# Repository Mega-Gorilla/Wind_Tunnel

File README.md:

# Wind Tunnel

**株式会社ながれ技術研究所の「オープンソース風洞 / MyWindTunnel」の吸込型風洞をベースに開発しています。** 原設計と風洞本体のCADは、[公式のMyWindTunnelページ](https://nagare-giken.jp/mywindtunnel/)から取得してください。原設計の公開に感謝します。

このリポジトリは、独自の電子回路・制御ソフト・追加固定部品と、その検証資料をまとめたものです。**公式配布の風洞CADは同梱しません。** 本体を含む結合CADや、その形状を変換・抽出したデータも配布対象にしません。独自部品のCAD、回路図、測定結果・図・報告書は別の公開対象として扱います。

現行基板は **Pico Carrier Rev E**、制御ソフトは **0.3.0 実機有限運転版・タッチ操作対応**です。

## 原設計からの変更

- ファンをARCTIC P12 MaxからP14 Pro PSTへ変更。
- Raspberry Pi Picoによるセンサー接続・回転数取得・ファン制御と、独自のPico Carrier基板を追加。
- Raspberry Pi上のタッチUIと、遠隔モードON/OFF・許可IP・APIトークン認証を備えたAPIを追加。
- 画面・基板・電源を固定する独自の樹脂部品を設計。

これらの変更を含む装置の測定結果は、原設計の性能値と同一ではありません。公式サイトの名称に「オープンソース」を含むことから、CADの再配布許諾を独自に推定しないでください。[第三者資料の扱い](THIRD_PARTY_NOTICES.md)を参照してください。

## 目的から探す

| 目的 | 開く資料 |
|---|---|
| 文書・試験結果の一覧 | [Docs 索引](Docs/README.md) |
| 基板を組み立てる | [Rev E 組立ガイド](Docs/assembly/WindTunnel_Pico_Carrier_RevE_Assembly_Guide.pdf) |
| センサーを接続する | [ピン別接続ガイド](Docs/assembly/WindTunnel_RevE_Sensor_Pin_Guide.pdf) |
| 回路・基板を編集する | [Electronics 案内](Electronics/README.md) |
| 樹脂部品とフレームを組み立てる | [組付けマニュアル](Docs/assembly/Item_Holder_Assembly_Manual.pdf)・[独自CAD](Mechanical/README.md) |
| UIとAPIを使う・開発する | [制御ソフト](software/control/README.md)・[基本設計](Docs/software/control-software/README.md) |
| 固定板のCFD結果を見る | [論文形式PDF](Docs/tests/cfd/2026-10-19_fixed_plate_refined/WindTunnel_FixedPlate_CFD_Paper_2026-10-19.pdf)・[詳細とデータ](Docs/tests/cfd/2026-10-19_fixed_plate_refined/REPORT.md) |

CFDは未収束の予備結果で、校正値には使用できません。実装済みの機能と、風速校正・長時間評価などの未完了事項は各資料で区別します。

## 公開する内容

| フォルダー | 内容 |
|---|---|
| `Docs` | 組立手順、設計説明、試験報告、調査、部品表 |
| `Electronics` | 現行KiCad回路・PCB、製造データ、Pico FW、診断ソース |
| `Mechanical` | 独自のホルダー・電源支持部品・圧入テスト片の単体CAD |
| `software` | UI・API・配備用ソースとテスト |
| `measurements` | 個人情報を含む管理ログを除いた測定データ |
| `analysis` | 解析コード・設定・比較図。風洞形状、格子、計算場、実行環境は別途準備 |
| `tools/repository` | 公開範囲・秘密情報・リンク・KiCad依存ファイルの検査 |

接続設定、実機IP・ユーザーを含む管理記録、個人情報を含む旧記録、外部ツール、キャッシュは公開しません。ローカルに残る除外ファイルはcloneには含まれません。公開前の確認内容は[公開準備記録](Docs/maintenance/publication-review/README.md)にまとめます。

## 開発と安全

開発手順は [CONTRIBUTING](CONTRIBUTING.md)、Git管理方針と初回pushは [Gitセットアップ](Docs/operations/GIT_SETUP.md)を参照してください。新しい試験報告は `Docs/tests/<分野>/<日付と試験名>/` へ保存し、測定条件と生データへの参照を付けます。

模擬テストは実機接続なしで実施できます。実機運転・配線変更・FW書込みは対象と停止条件を確認して行います。ソフト停止は安全認証された非常停止ではありません。

本プロジェクト独自部分の公開ライセンスは未選定です。公開リポジトリであることと、任意の再利用を許諾することは異なります。第三者部分の既存のライセンス・著作権表記は維持します。

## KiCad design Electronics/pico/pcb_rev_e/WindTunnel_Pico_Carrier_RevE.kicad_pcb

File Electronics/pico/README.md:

# Pico Carrier Rev Eとファームウェア

初代Raspberry Pi Pico（RP2040）を使用する現行構成。製造正本は[Rev E KiCadプロジェクト](pcb_rev_e/WindTunnel_Pico_Carrier_RevE.kicad_pro)です。旧Rev C/Dの接続図を現行の製造指示として使用しないでください。

- [回路図](pcb_rev_e/WindTunnel_Pico_Carrier_RevE.kicad_sch)・[基板](pcb_rev_e/WindTunnel_Pico_Carrier_RevE.kicad_pcb)
- [現行の制御ファームウェア](firmware/control_main.py)
- [基板組立](../../Docs/assembly/WindTunnel_Pico_Carrier_RevE_Assembly_Guide.pdf)・[センサーピン接続](../../Docs/assembly/WindTunnel_RevE_Sensor_Pin_Guide.pdf)
- [実機有限運転版の検証記録](../../Docs/tests/software/pico-control/README.md)
- [センサーとファンの段階試験](../../Docs/tests/fan-sensors/2026-10-17/TEST_RESULT.txt)

Picoがセンサー取得、Tach計数、PWM生成、通信断時の停止を担当し、PiとはUSBで接続します。FWとUI/APIの通信プロトコルを一致させて使用してください。停止専用の旧FWを現行制御版と混用しないでください。

`diagnostics` と測定記録内のスクリプトは試験用で、ファン駆動や保存済みFWの変更を伴うものがあります。内容確認のために実行せず、配線・電源・停止条件を確認してから使用します。センサー読値やTach換算RPMの機能確認は、風速・回転数の独立校正ではありません。

外部12 V、Pi給電、PicoのUSB・3.3 Vを混同しないでください。SW1はファン電源の手動スイッチで、安全認証された非常停止ではありません。初回配線・保守は無通電で行い、運転時はファン周囲を保護します。

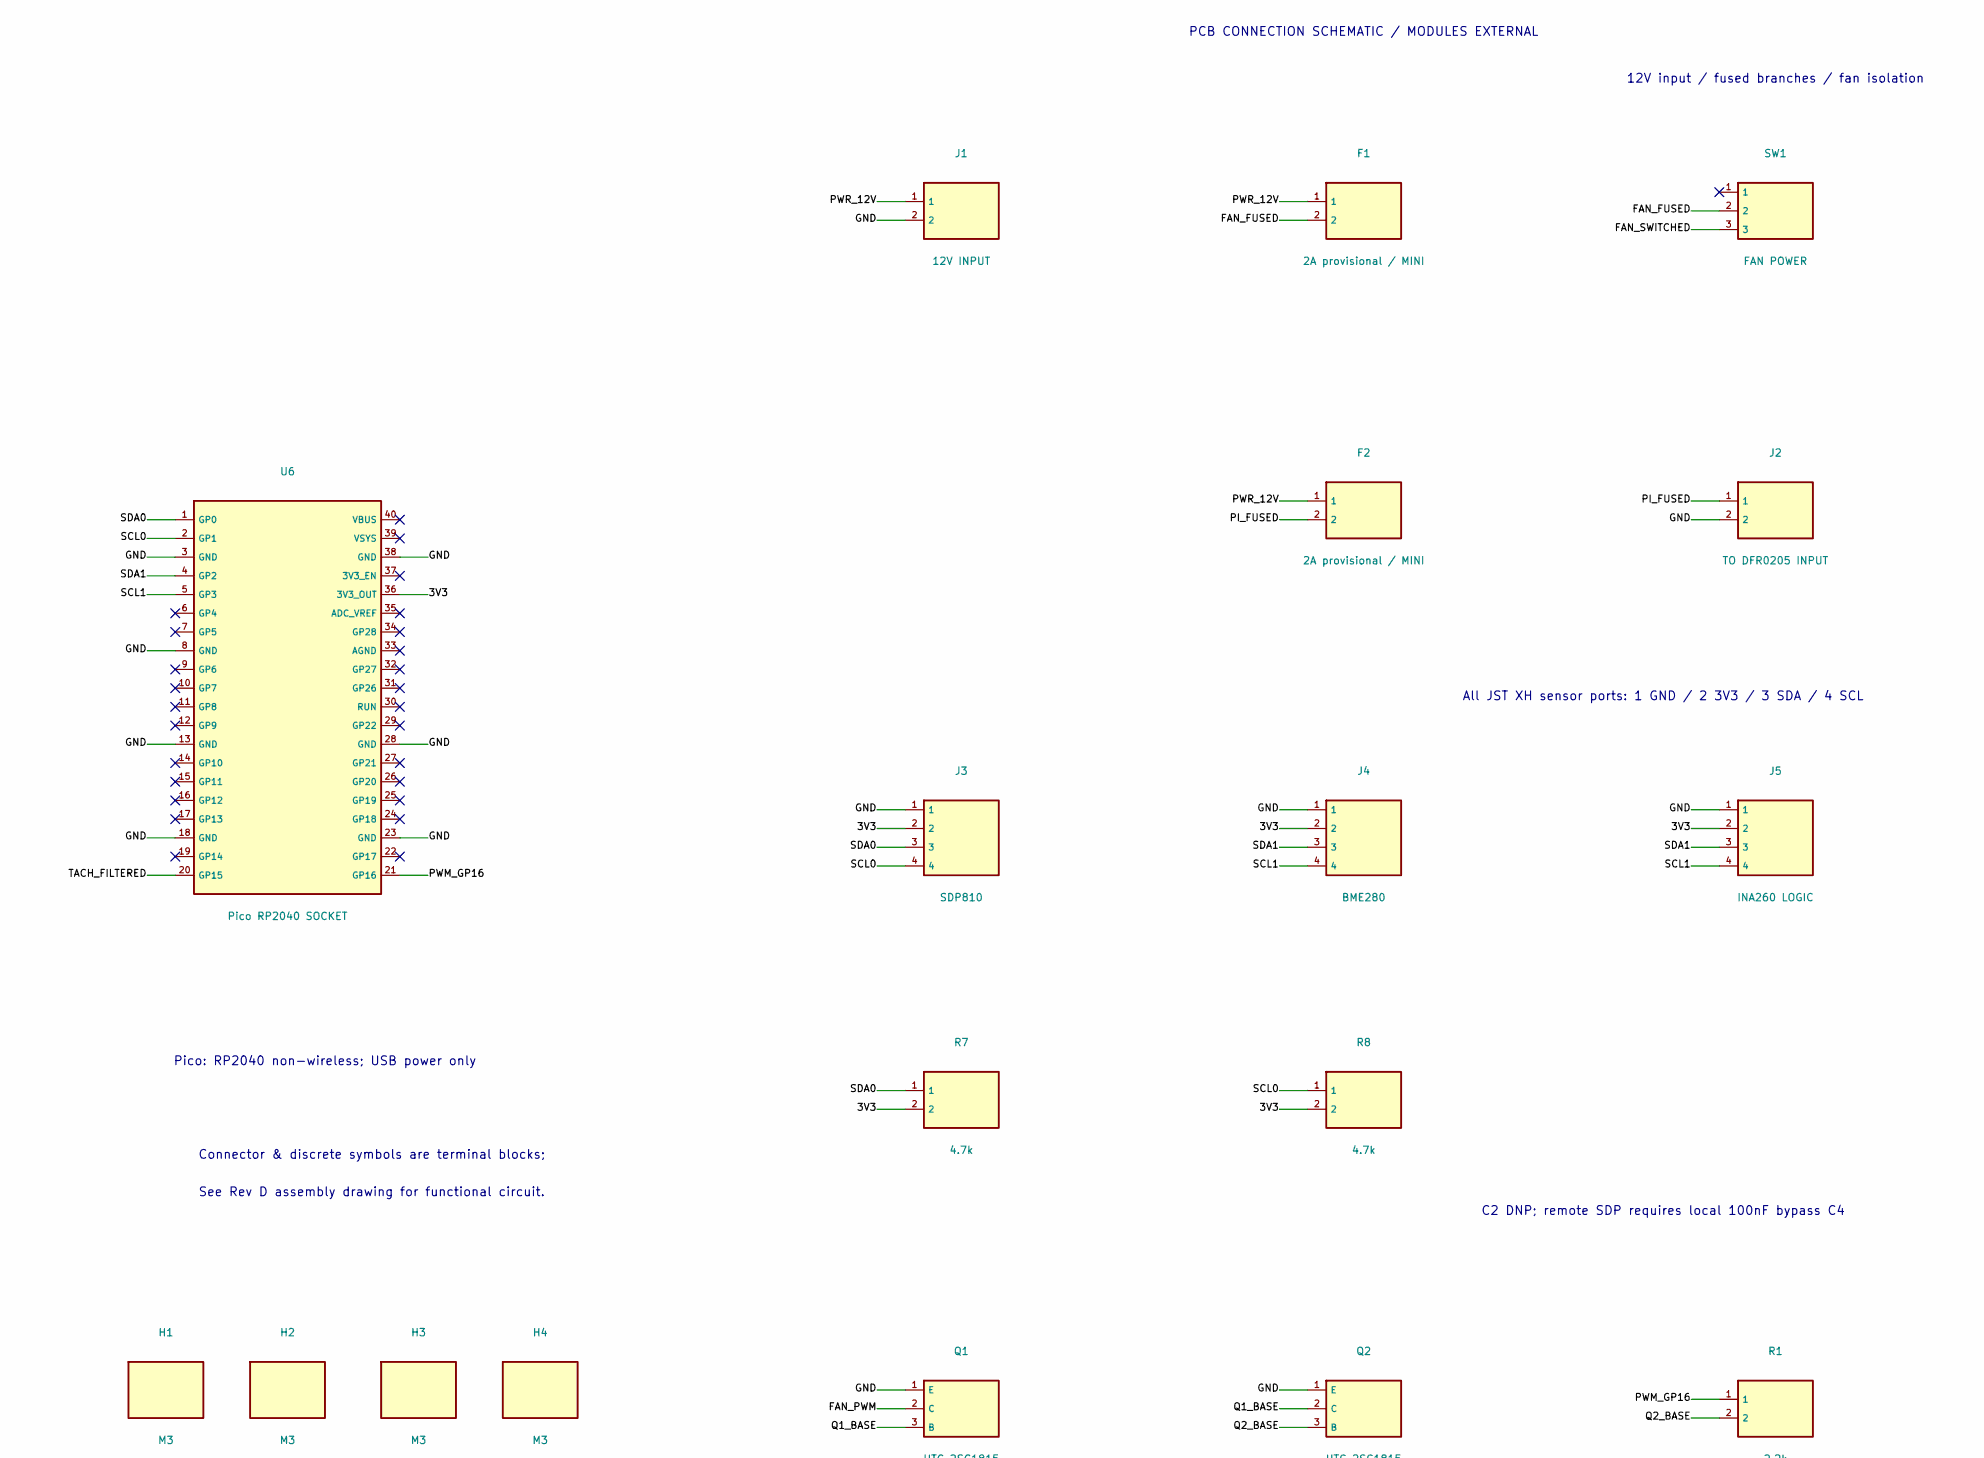
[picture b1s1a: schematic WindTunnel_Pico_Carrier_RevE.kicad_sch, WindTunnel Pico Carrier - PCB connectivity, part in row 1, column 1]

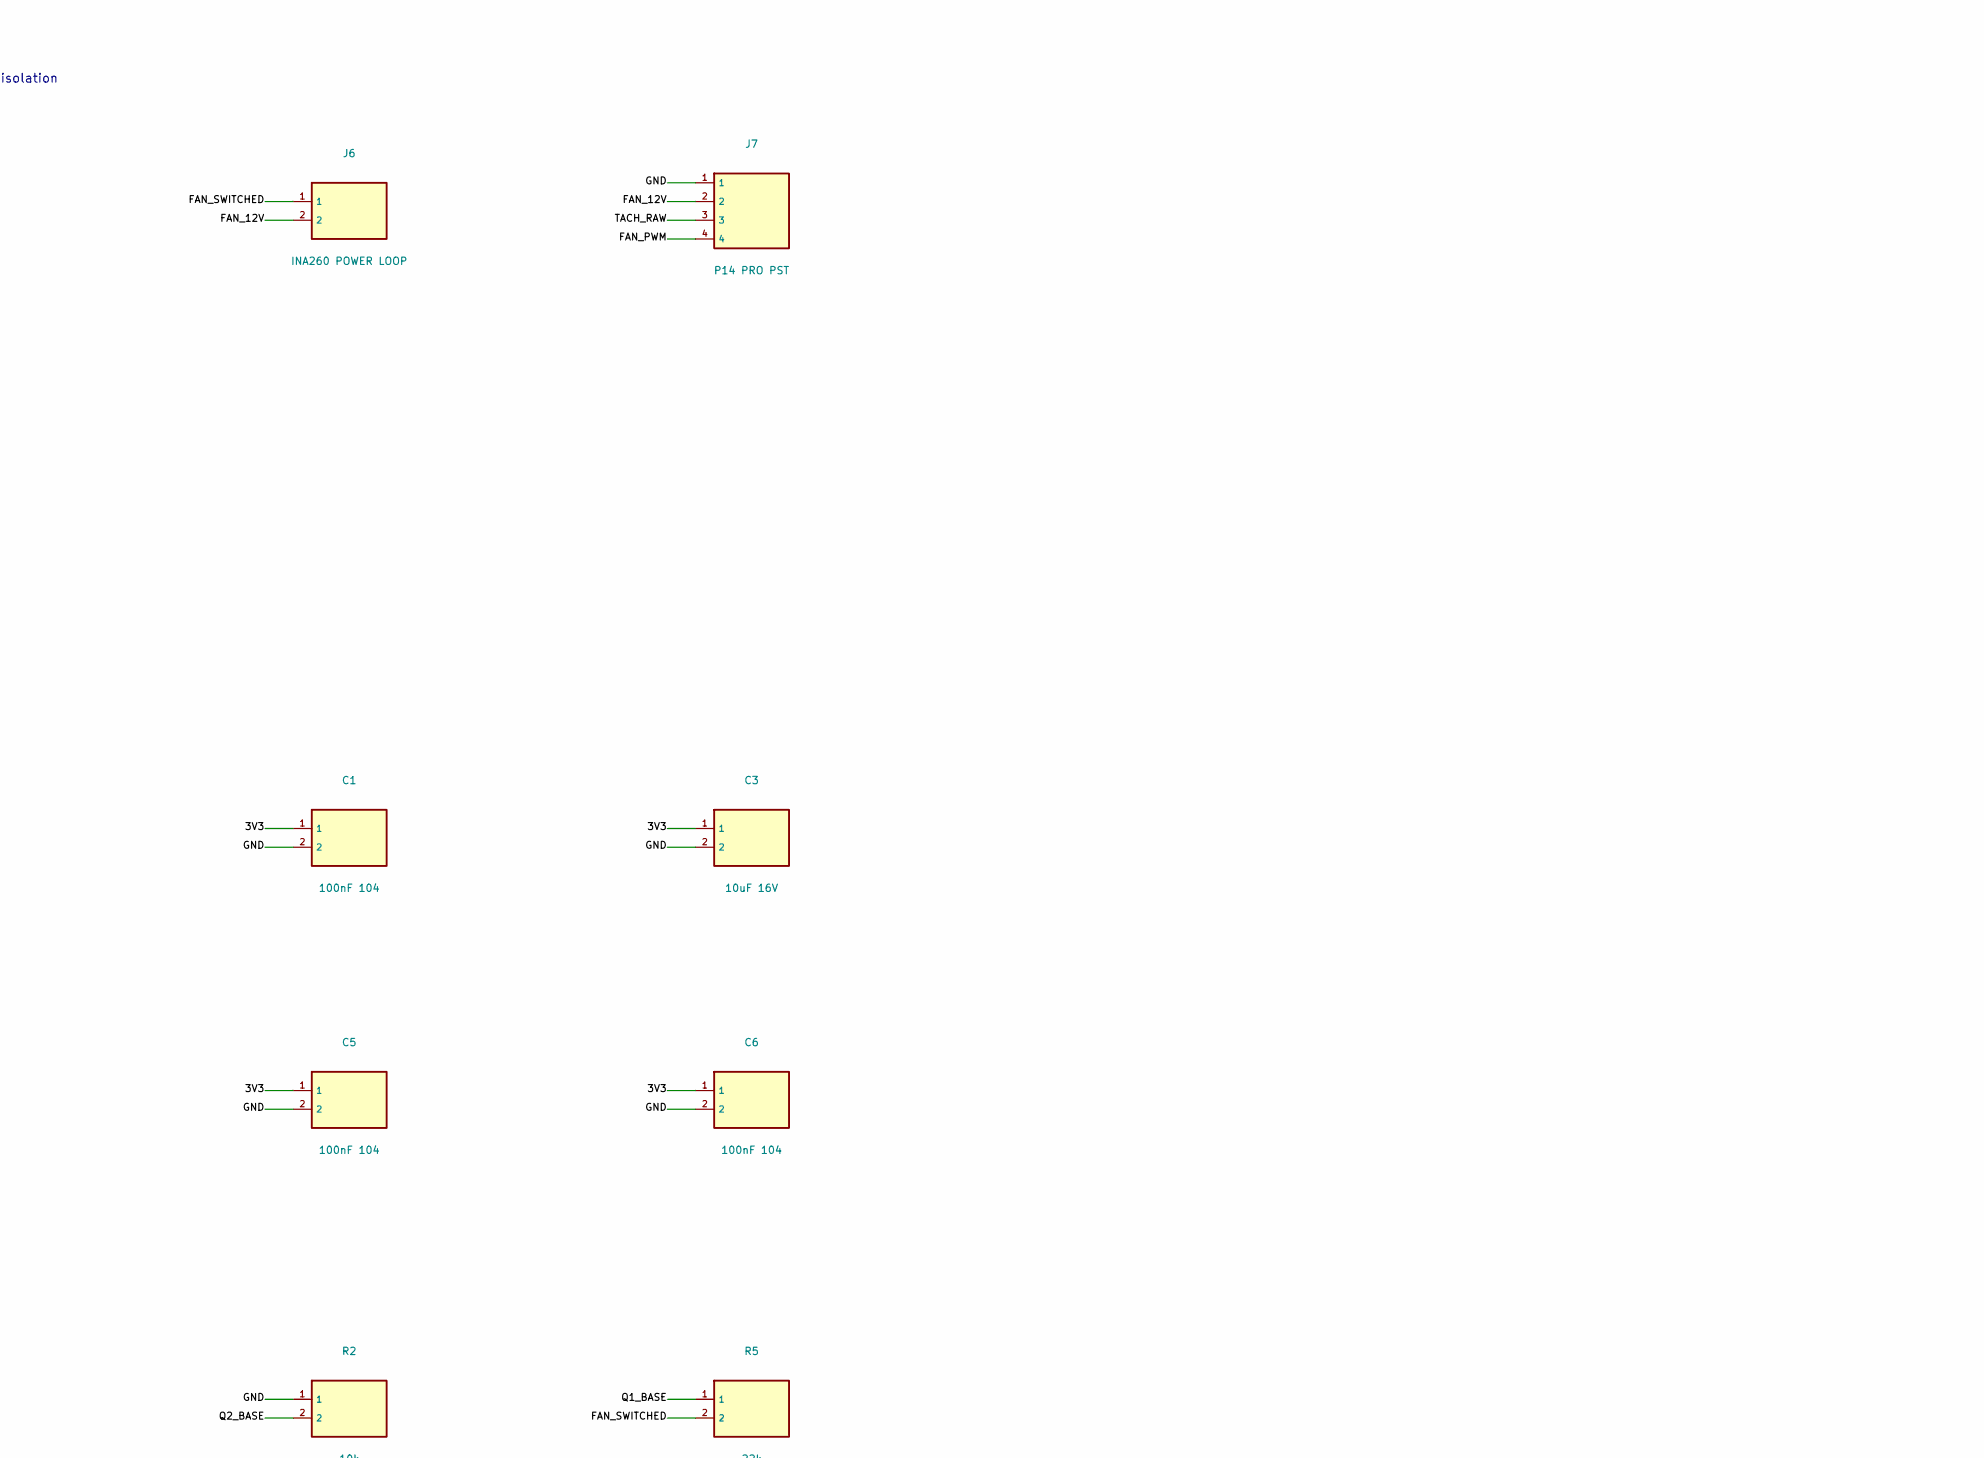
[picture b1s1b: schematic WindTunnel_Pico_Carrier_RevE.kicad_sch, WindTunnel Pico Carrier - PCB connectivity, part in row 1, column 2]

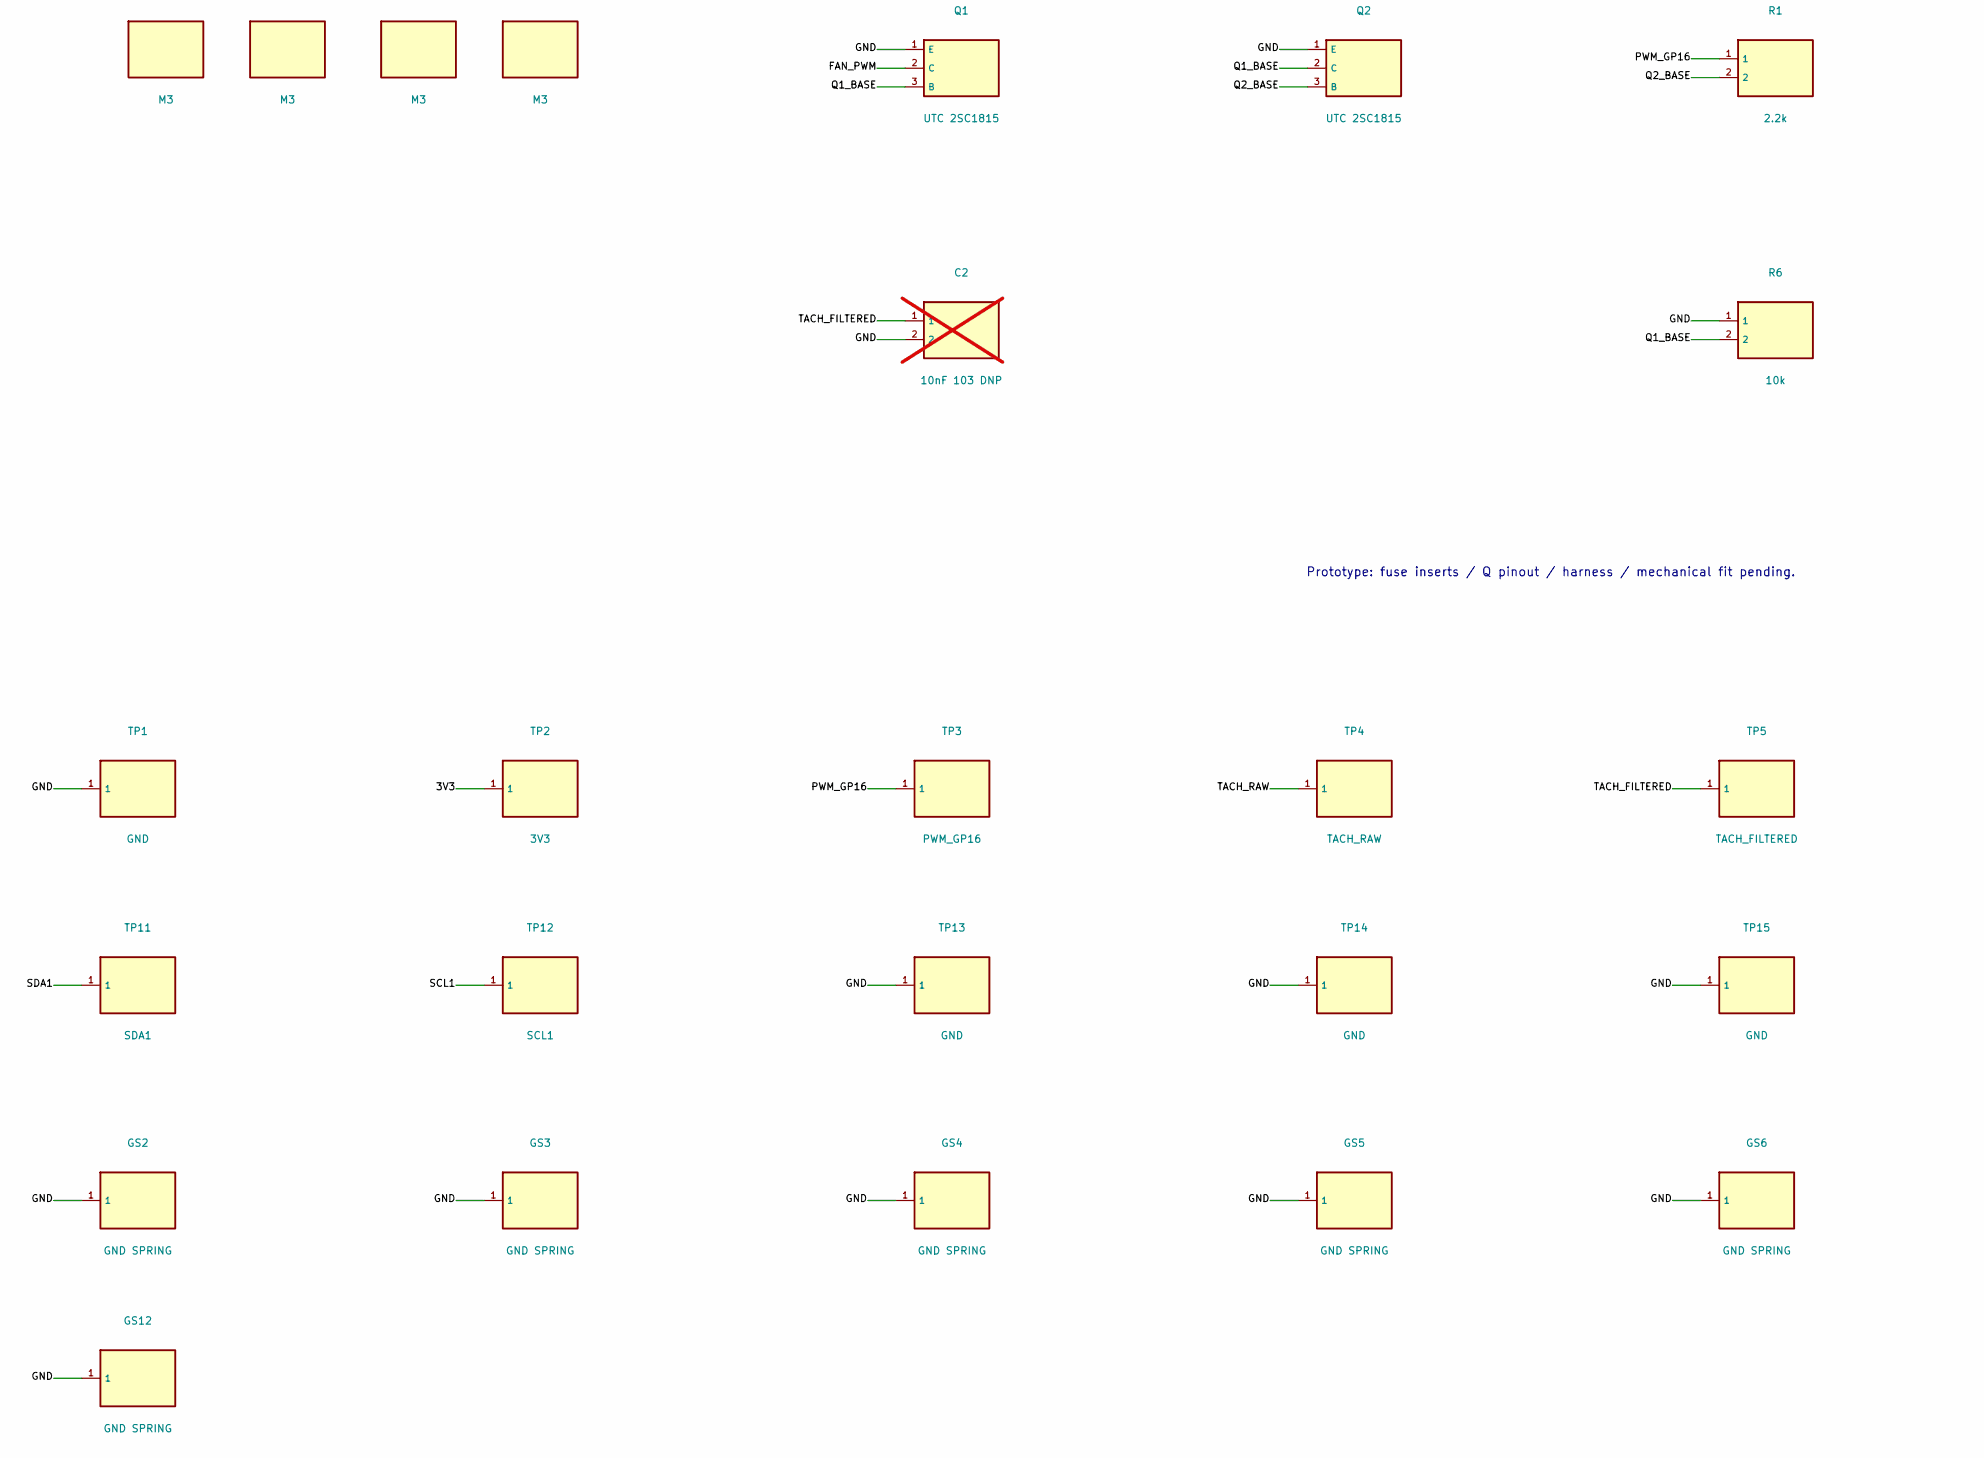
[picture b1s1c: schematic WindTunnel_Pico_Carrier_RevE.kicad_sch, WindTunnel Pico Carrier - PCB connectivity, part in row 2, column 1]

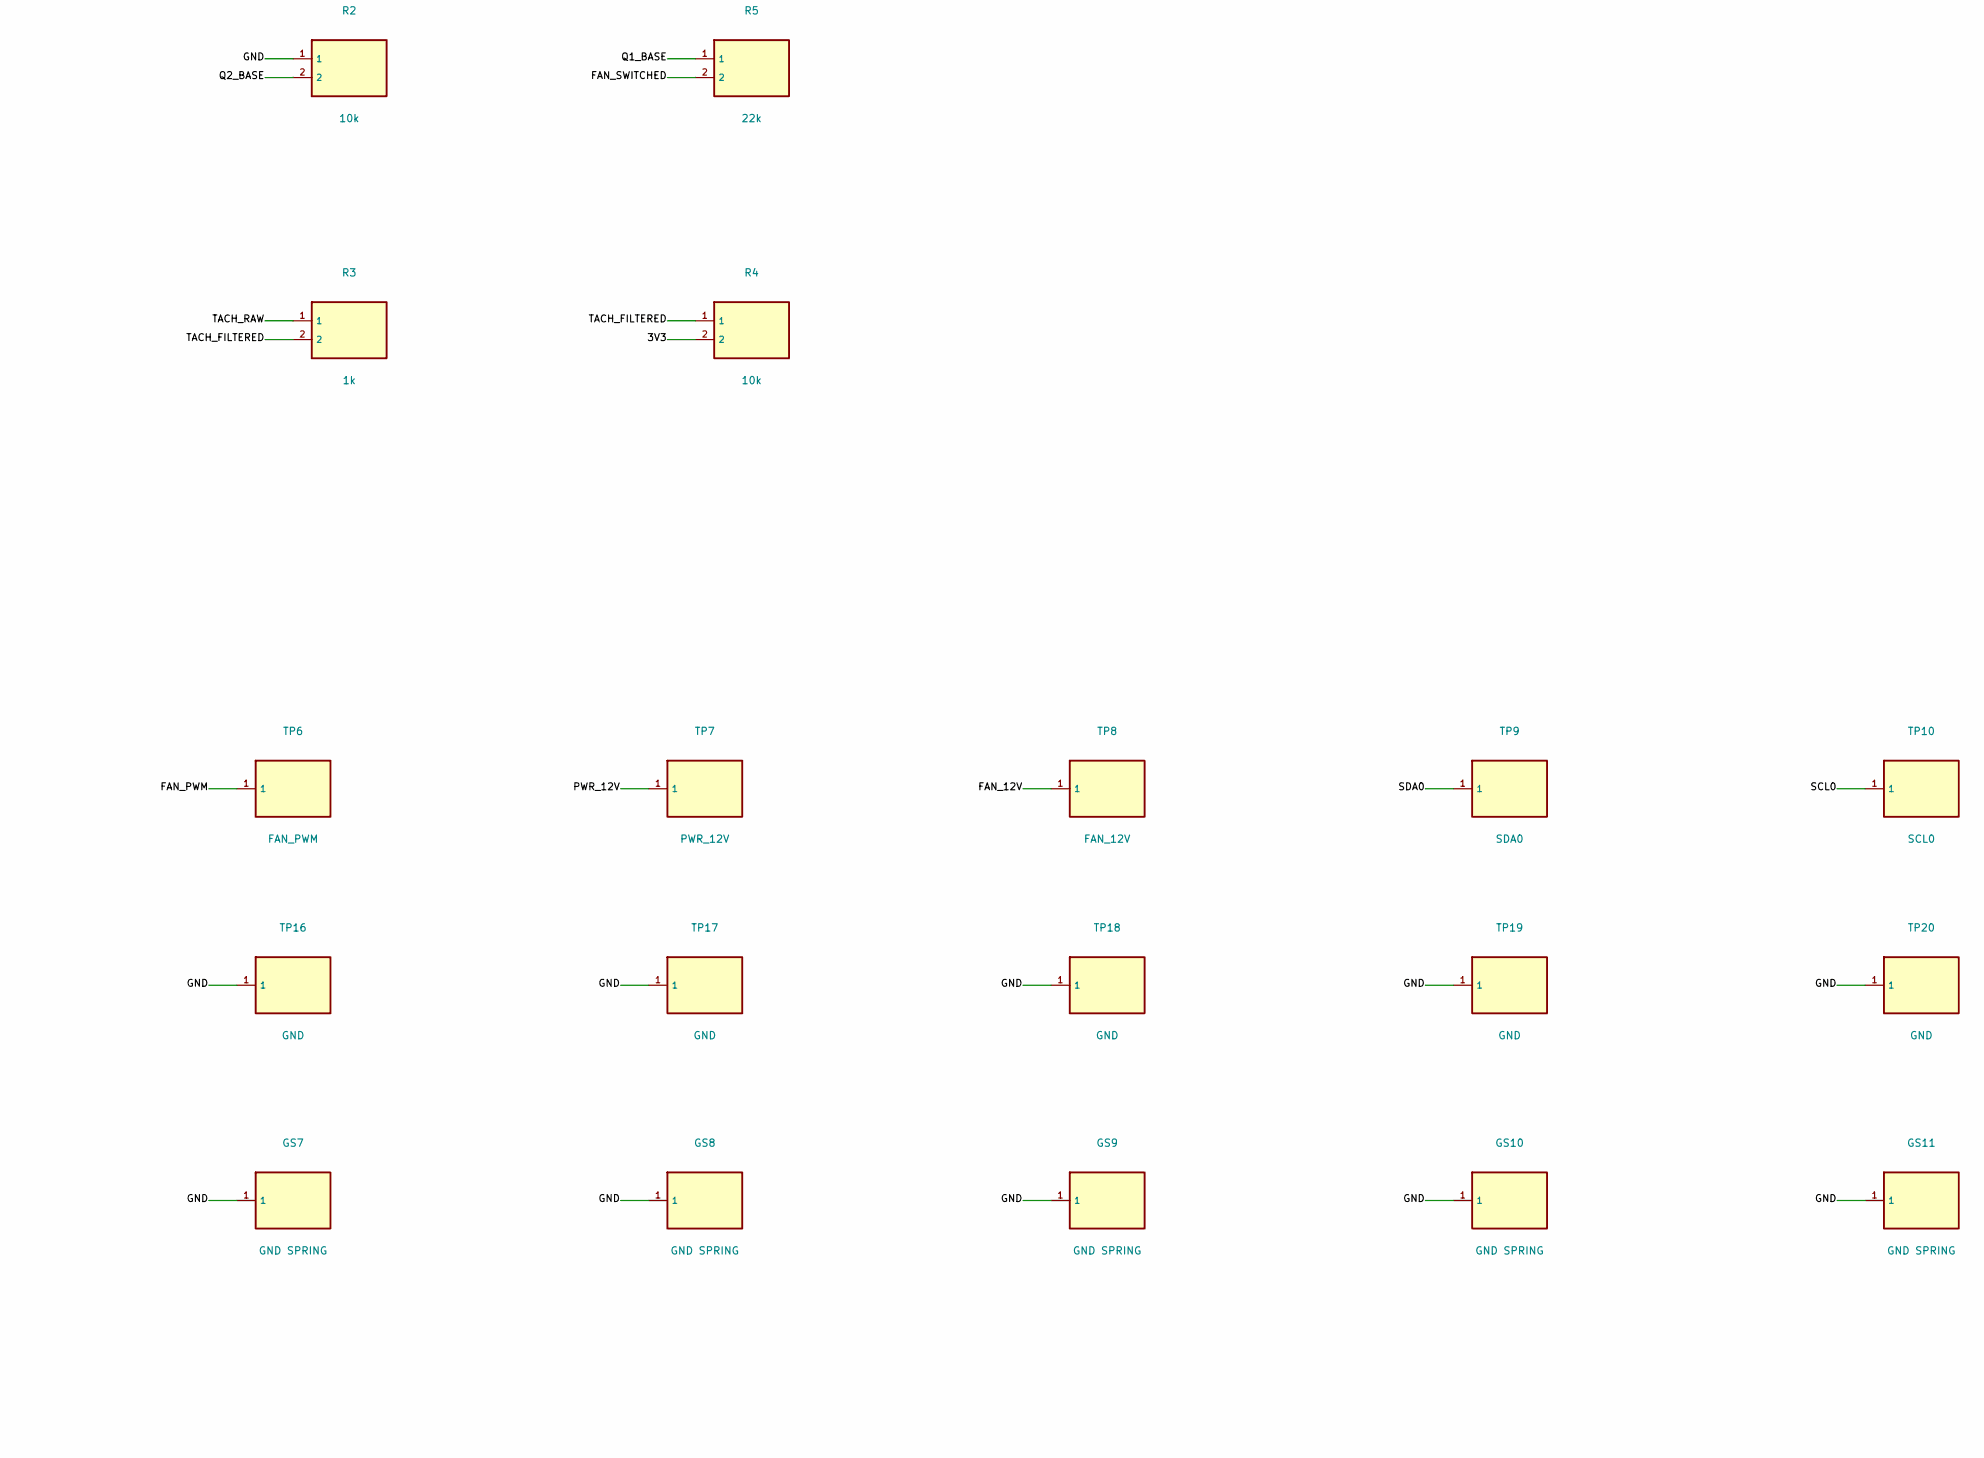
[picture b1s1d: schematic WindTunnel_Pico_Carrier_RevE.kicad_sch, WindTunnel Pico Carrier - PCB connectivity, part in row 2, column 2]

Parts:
C1, C5, C6: 100nF 104; C_Vishay_K15_H5; MPN Vishay K104K15X7RF5TH5
C2: 10nF 103 DNP; C_Disc_D5.0mm_W2.5mm_P5.00mm; not fitted
C3: 10uF 16V; CP_Radial_D5.0mm_P2.00mm
F1, F2: 2A provisional / MINI; Fuseholder_Blade_Mini_Keystone_3568; MPN Keystone 3568
GS2, GS3, GS4, GS5, GS6, GS7, GS8, GS9, GS10, GS11, GS12: GND SPRING; TestPoint_THTPad_D2.0mm_Drill1.0mm
H1, H2, H3, H4: M3; MountingHole_3.2mm_M3
J1: 12V INPUT; TerminalBlock_Phoenix_MKDS-1,5-2-5.08_1x02_P5.08mm_Horizont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; MPN Phoenix Contact 1715721
J2: TO DFR0205 INPUT; TerminalBlock_Phoenix_MKDS-1,5-2-5.08_1x02_P5.08mm_Horizont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; MPN Phoenix Contact 1715721
J3: SDP810; JST_XH_B4B-XH-A_1x04_P2.50mm_Vertical; MPN JST B4B-XH-A (LF)(SN)
J4: BME280; JST_XH_B4B-XH-A_1x04_P2.50mm_Vertical; MPN JST B4B-XH-A (LF)(SN)
J5: INA260 LOGIC; JST_XH_B4B-XH-A_1x04_P2.50mm_Vertical; MPN JST B4B-XH-A (LF)(SN)
J6: INA260 POWER LOOP; TerminalBlock_Phoenix_MKDS-1,5-2-5.08_1x02_P5.08mm_Horizont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; MPN Phoenix Contact 1715721
J7: P14 PRO PST; FanPinHeader_1x04_P2.54mm_Vertical; MPN Molex 47053-1000
Q1, Q2: UTC 2SC1815; TO-92_Inline_Wide; MPN UTC 2SC1815
R1: 2.2k; R_Axial_DIN0207_L6.3mm_D2.5mm_P10.16mm_Horizontal
R2, R4, R6: 10k; R_Axial_DIN0207_L6.3mm_D2.5mm_P10.16mm_Horizontal
R3: 1k; R_Axial_DIN0207_L6.3mm_D2.5mm_P10.16mm_Horizontal
R5: 22k; R_Axial_DIN0207_L6.3mm_D2.5mm_P10.16mm_Horizontal
R7, R8: 4.7k; R_Axial_DIN0207_L6.3mm_D2.5mm_P10.16mm_Horizontal
SW1: FAN POWER; SW_NKK_MN12SS1W03; MPN NKK MN12SS1W03
TP1, TP13, TP14, TP15, TP16, TP17, TP18, TP19, TP20: GND; TestPoint_Keystone_5001_Miniature; MPN Keystone 5001
TP2: 3V3; TestPoint_Keystone_5000_Miniature; MPN Keystone 5000
TP3: PWM_GP16; TestPoint_Keystone_5002_Miniature; MPN Keystone 5002
TP4: TACH_RAW; TestPoint_Keystone_5002_Miniature; MPN Keystone 5002
TP5: TACH_FILTERED; TestPoint_Keystone_5002_Miniature; MPN Keystone 5002
TP6: FAN_PWM; TestPoint_Keystone_5002_Miniature; MPN Keystone 5002
TP7: PWR_12V; TestPoint_Keystone_5000_Miniature; MPN Keystone 5000
TP8: FAN_12V; TestPoint_Keystone_5000_Miniature; MPN Keystone 5000
TP9: SDA0; TestPoint_Keystone_5002_Miniature; MPN Keystone 5002
TP10: SCL0; TestPoint_Keystone_5002_Miniature; MPN Keystone 5002
TP11: SDA1; TestPoint_Keystone_5002_Miniature; MPN Keystone 5002
TP12: SCL1; TestPoint_Keystone_5002_Miniature; MPN Keystone 5002
U6: Pico RP2040 SOCKET; RaspberryPi_Pico_NonWireless_Socket; MPN Raspberry Pi Pico + 2x Harwin M20-78220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

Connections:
/3V3: C1.1, C3.1, C5.1, C6.1, J3.2, J4.2, J5.2, R4.2, R7.2, R8.2, TP2.1 (1_1), U6.36 (3V3_OUT)
/FAN_12V: J6.2, J7.2, TP8.1 (1_1)
/FAN_FUSED: F1.2, SW1.2
/FAN_PWM: J7.4, Q1.2 (C), TP6.1 (1_1)
/FAN_SWITCHED: J6.1, R5.2, SW1.3
/GND: C1.2, C2.2, C3.2, C5.2, C6.2, GS2.1 (1_1), GS3.1 (1_1), GS4.1 (1_1), GS5.1 (1_1), GS6.1 (1_1), GS7.1 (1_1), GS8.1 (1_1), GS9.1 (1_1), GS10.1 (1_1), GS11.1 (1_1), GS12.1 (1_1), J1.2, J2.2, J3.1, J4.1, J5.1, J7.1, Q1.1 (E), Q2.1 (E), R2.1, R6.1, TP1.1 (1_1), TP13.1 (1_1), TP14.1 (1_1), TP15.1 (1_1), TP16.1 (1_1), TP17.1 (1_1), TP18.1 (1_1), TP19.1 (1_1), TP20.1 (1_1), U6.3 (GND), U6.8 (GND), U6.13 (GND), U6.18 (GND), U6.23 (GND), U6.28 (GND), U6.38 (GND)
/PI_FUSED: F2.2, J2.1
/PWM_GP16: R1.1, TP3.1 (1_1), U6.21 (GP16)
/PWR_12V: F1.1, F2.1, J1.1, TP7.1 (1_1)
/Q1_BASE: Q1.3 (B), Q2.2 (C), R5.1, R6.2
/Q2_BASE: Q2.3 (B), R1.2, R2.2
/SCL0: J3.4, R8.1, TP10.1 (1_1), U6.2 (GP1)
/SCL1: J4.4, J5.4, TP12.1 (1_1), U6.5 (GP3)
/SDA0: J3.3, R7.1, TP9.1 (1_1), U6.1 (GP0)
/SDA1: J4.3, J5.3, TP11.1 (1_1), U6.4 (GP2)
/TACH_FILTERED: C2.1, R3.2, R4.1, TP5.1 (1_1), U6.20 (GP15)
/TACH_RAW: J7.3, R3.1, TP4.1 (1_1)

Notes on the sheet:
PCB CONNECTION SCHEMATIC / MODULES EXTERNAL
12V input / fused branches / fan isolation
All JST XH sensor ports: 1 GND / 2 3V3 / 3 SDA / 4 SCL
C2 DNP; remote SDP requires local 100nF bypass C4
Pico: RP2040 non-wireless; USB power only
Connector & discrete symbols are terminal blocks;
See Rev D assembly drawing for functional circuit.
Prototype: fuse inserts / Q pinout / harness / mechanical fit pending.

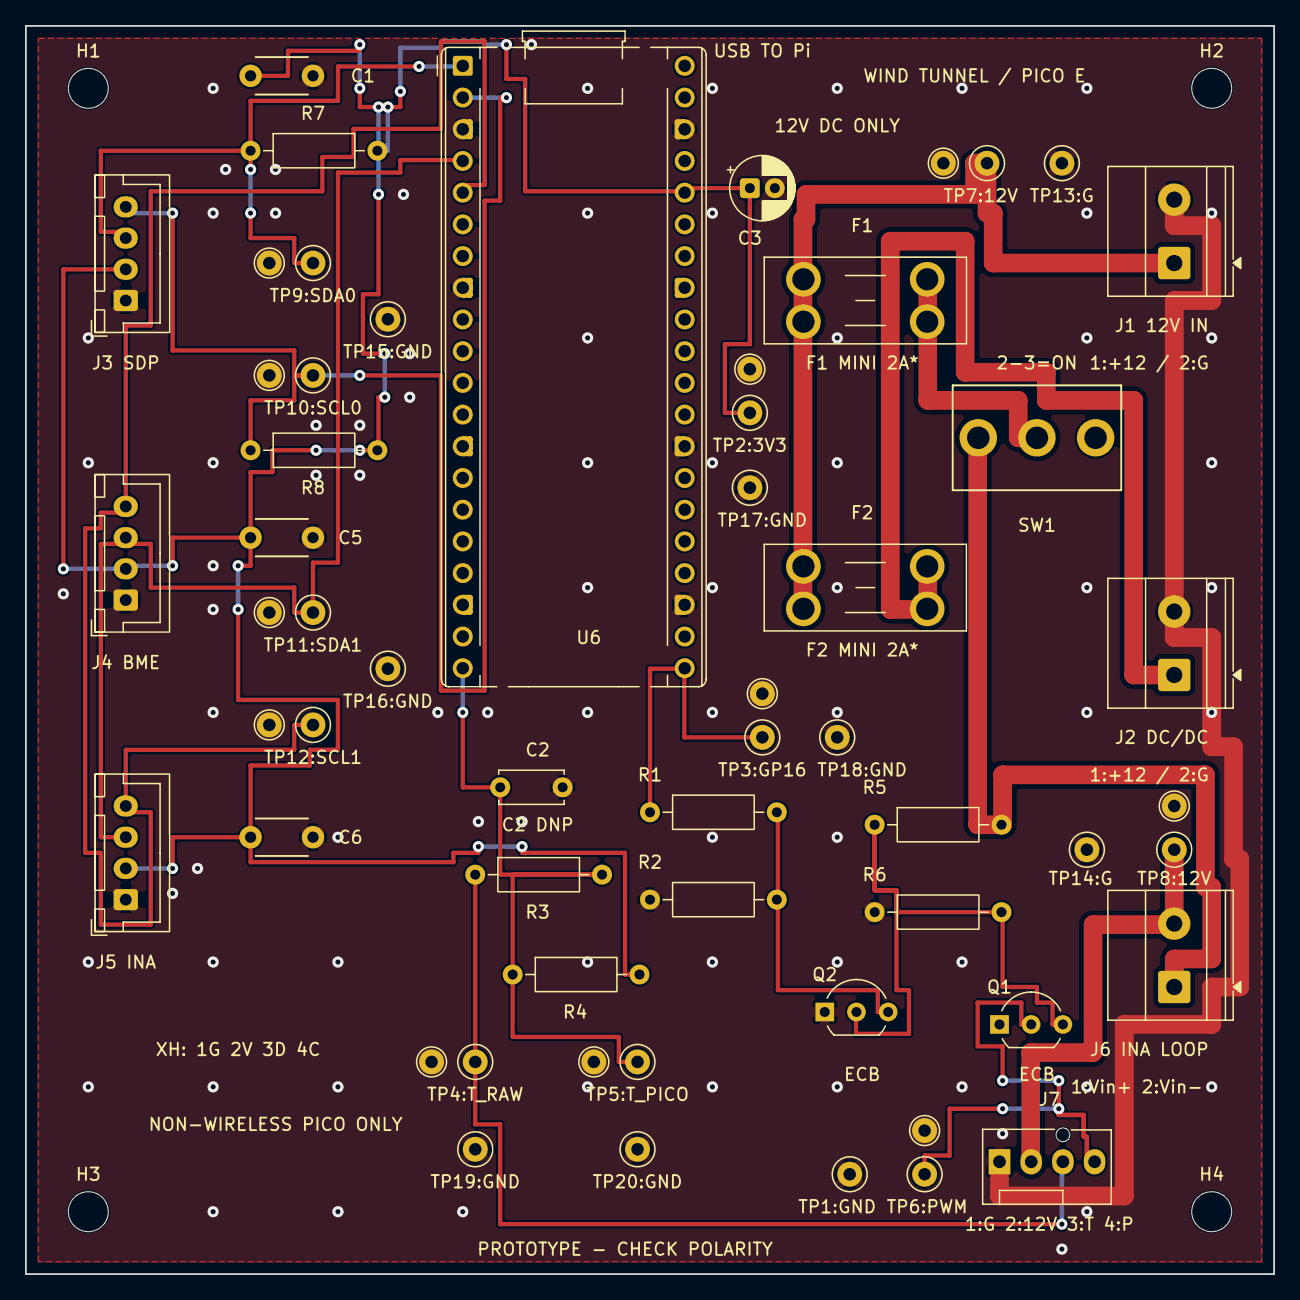
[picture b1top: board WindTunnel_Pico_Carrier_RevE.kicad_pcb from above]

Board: 2 copper layers, 100.0 x 100.0 mm, 61 parts (0 on the bottom side), 17 nets.
